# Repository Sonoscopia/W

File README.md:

# W
W: Staged concert for robotic orchestra and puppets
A co-creation of Sonoscopia and Teatro de Ferro
Homepage is [here](https://sonoscopia.pt/en/works/w-en/)

## Contents of this repository: 
- SRC01: 8 channel relay controller with MIDI IN/THRU and 8 arcade buttons
- Servo8: 8 channel servo controller with MIDI IN/THRU and 8 knobs
- Stepper5: 5 channel stepper motor controller with MIDI IN/THRU and 5 encoders (if I remember correctly...)

## Description
W is a staged concert for puppets, robotic orchestra and video that departs from the theme of work, human liberation and the logic of power, subjugation and domination initiated with the development of Phobos – Dysfunctional Robotic Orchestra. These issues, exposed in a subliminal and essentially musical way in Phobos’ original conception, now move to a clear dramaturgical level and are reinforced by the text, gesture, body, video and scenic space that highlights all the developed sound elements.

W is the physical symbol of the work and this staged concert is itself the result of thousands of hours of work. But what is work anyway?
The play traverses a diversity of places and imaginaries where this strange form of life thrives, simultaneously liberating and oppressive, which has transformed the world into a large shipyard, a large shopping centre.

Somewhere between the expulsion from the earthly paradise, from which we began to eat bread made with the sweat of our brows, and the hegemony of the neoliberal paradigm – in which sweat, bread or face are mere assets that each individual entrepreneur may or may not access – there is a place to look. W!

## Credits
- Project conception and management: Gustavo Costa
- Staging, Scenography and Dramaturgy – Igor Gandra
- Plastic Realization and Construction – Eduardo Mendes
- Light design: Mariana Figueroa
- Composition and musical direction: Gustavo Costa
- Interpretation: Adriana Romero, Alberto Lopes, Carla Veloso, Eduardo Mendes, Gustavo Costa, Henrique Fernandes, Igor Gandra, Jorge Quintela and Tiago Ângelo
- Support for electronics and programming: Tiago Ângelo
- Instrument building: Alberto Lopes, Henrique Fernandes and Gustavo Costa
- Video: Jorge Quintela
- Construction of the scenography, puppets and props: Eduardo Mendes, Hernâni Miranda, Gonçalo Silva (trainee at the Professional School of the Campanhã Youth Center), Solveig Phyllis Rocher, Américo Castanheira
- Executive Production: Carla Veloso and Patrícia Caveiro
- Production support: Catarina Lopes
- Production: Sonoscopy and Teatro de Ferro
- Co-production: Teatro Municipal do Porto
- Partnership: 23 Miles
- Project supported by the Portuguese Republic – Culture/Direção-Geral das Artes.
- Acknowledgements: Hugo de Almeida Pinho, Regina Guimarães

## LICENSE
[![CC BY-NC 4.0][cc-by-nc-shield]][cc-by-nc]

This work is licensed under a
[Creative Commons Attribution-NonCommercial 4.0 International License][cc-by-nc].

[![CC BY-NC 4.0][cc-by-nc-image]][cc-by-nc]

[cc-by-nc]: https://creativecommons.org/licenses/by-nc/4.0/
[cc-by-nc-image]: https://licensebuttons.net/l/by-nc/4.0/88x31.png
[cc-by-nc-shield]: https://img.shields.io/badge/License-CC%20BY--NC%204.0-lightgrey.svg

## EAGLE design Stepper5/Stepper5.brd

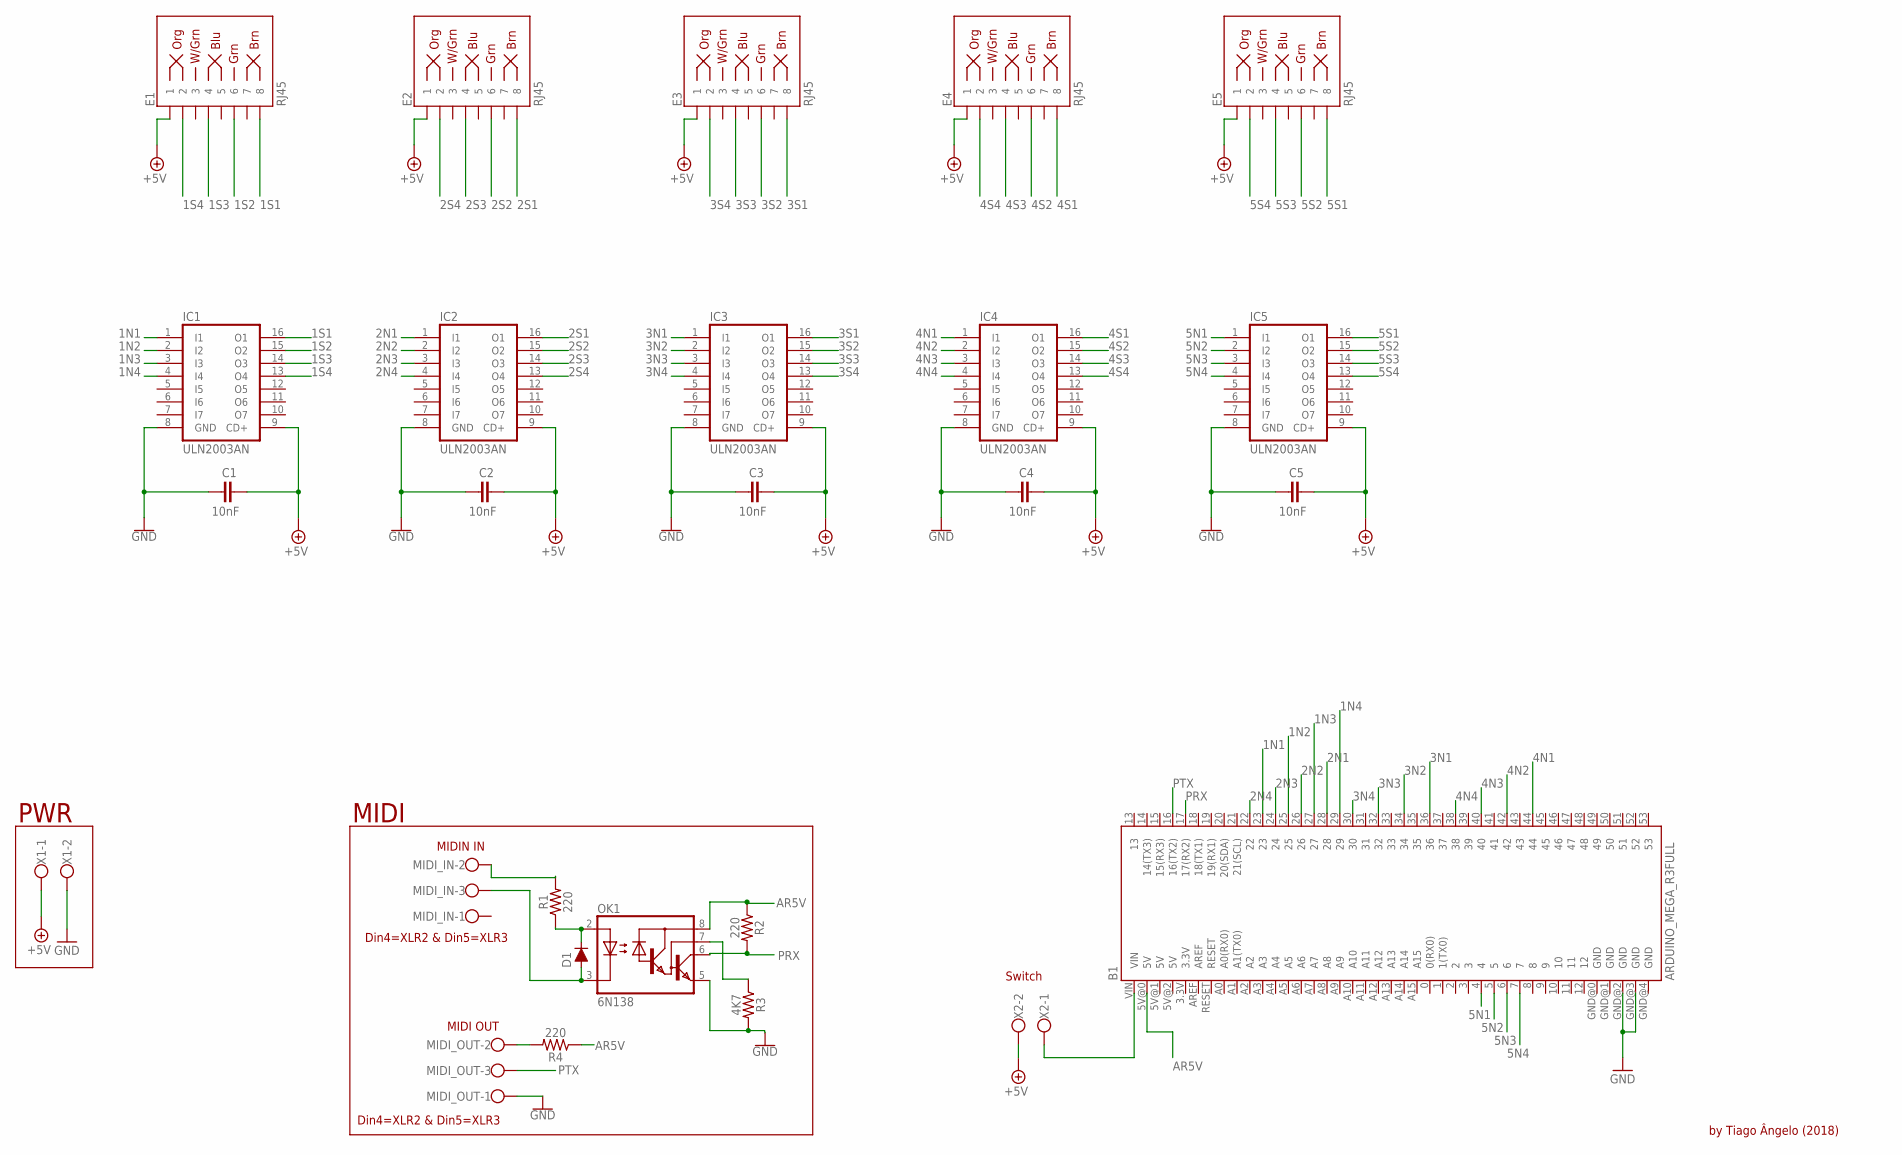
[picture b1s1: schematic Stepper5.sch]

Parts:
B1: ARDUINO_MEGA_R3FULL; ARDUINO_MEGA
C1, C2, C3, C4, C5: 10nF; C5B2.5
D1: 200mA/100V/1V; DIODE-1N4148
E1, E2, E3, E4, E5: RJ45; RJ45-8
IC1, IC2, IC3, IC4, IC5: ULN2003AN; DIL16
MIDI_IN: W237-103
MIDI_OUT: W237-103
OK1: 6N138; DIL08
R1, R2, R4: 220; AXIAL-0.3
R3: 4K7; AXIAL-0.3
X1, X2: W237-102

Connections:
1N1: B1.23, IC1.1 (I1)
1N2: B1.25, IC1.2 (I2)
1N3: B1.27, IC1.3 (I3)
1N4: B1.29, IC1.4 (I4)
1S1: E1.8, IC1.16 (O1)
1S2: E1.6, IC1.15 (O2)
1S3: E1.4, IC1.14 (O3)
1S4: E1.2, IC1.13 (O4)
2N1: B1.28, IC2.1 (I1)
2N2: B1.26, IC2.2 (I2)
2N3: B1.24, IC2.3 (I3)
2N4: B1.22, IC2.4 (I4)
2S1: E2.8, IC2.16 (O1)
2S2: E2.6, IC2.15 (O2)
2S3: E2.4, IC2.14 (O3)
2S4: E2.2, IC2.13 (O4)
3N1: B1.36, IC3.1 (I1)
3N2: B1.34, IC3.2 (I2)
3N3: B1.32, IC3.3 (I3)
3N4: B1.30, IC3.4 (I4)
3S1: E3.8, IC3.16 (O1)
3S2: E3.6, IC3.15 (O2)
3S3: E3.4, IC3.14 (O3)
3S4: E3.2, IC3.13 (O4)
4N1: B1.44, IC4.1 (I1)
4N2: B1.42, IC4.2 (I2)
4N3: B1.40, IC4.3 (I3)
4N4: B1.38, IC4.4 (I4)
4S1: E4.8, IC4.16 (O1)
4S2: E4.6, IC4.15 (O2)
4S3: E4.4, IC4.14 (O3)
4S4: E4.2, IC4.13 (O4)
5N1: B1.4, IC5.1 (I1)
5N2: B1.5, IC5.2 (I2)
5N3: B1.6, IC5.3 (I3)
5N4: B1.7, IC5.4 (I4)
5S1: E5.8, IC5.16 (O1)
5S2: E5.6, IC5.15 (O2)
5S3: E5.4, IC5.14 (O3)
5S4: E5.2, IC5.13 (O4)
+5V: C1.2, C2.2, C3.2, C4.2, C5.2, E1.1, E2.1, E3.1, E4.1, E5.1, IC1.9 (CD+), IC2.9 (CD+), IC3.9 (CD+), IC4.9 (CD+), IC5.9 (CD+), X1.1, X2.2
AR5V: B1.5V@0 (5V), OK1.8 (VCC), R2.P$1 (1), R4.P$1 (1)
GND: B1.GND@2 (GND), B1.GND@3 (GND), C1.1, C2.1, C3.1, C4.1, C5.1, IC1.8 (GND), IC2.8 (GND), IC3.8 (GND), IC4.8 (GND), IC5.8 (GND), MIDI_OUT.1, OK1.5 (GND), R3.P$2 (2), X1.2
unnamed: B1.VIN, X2.1
unnamed: MIDI_OUT.2, R4.P$2 (2)
unnamed: D1.A, MIDI_IN.3, OK1.3 (C)
unnamed: D1.C, OK1.2 (A), R1.P$1 (1)
unnamed: MIDI_IN.2, R1.P$2 (2)
unnamed: OK1.7 (VB), R3.P$1 (1)
PRX: B1.17 (17(RX2)), OK1.6 (VO), R2.P$2 (2)
PTX: B1.16 (16(TX2)), MIDI_OUT.3

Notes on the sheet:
Din4=XLR2 & Din5=XLR3
MIDI OUT
MIDIN IN
MIDI
PWR
by Tiago Ângelo (2018)
Switch

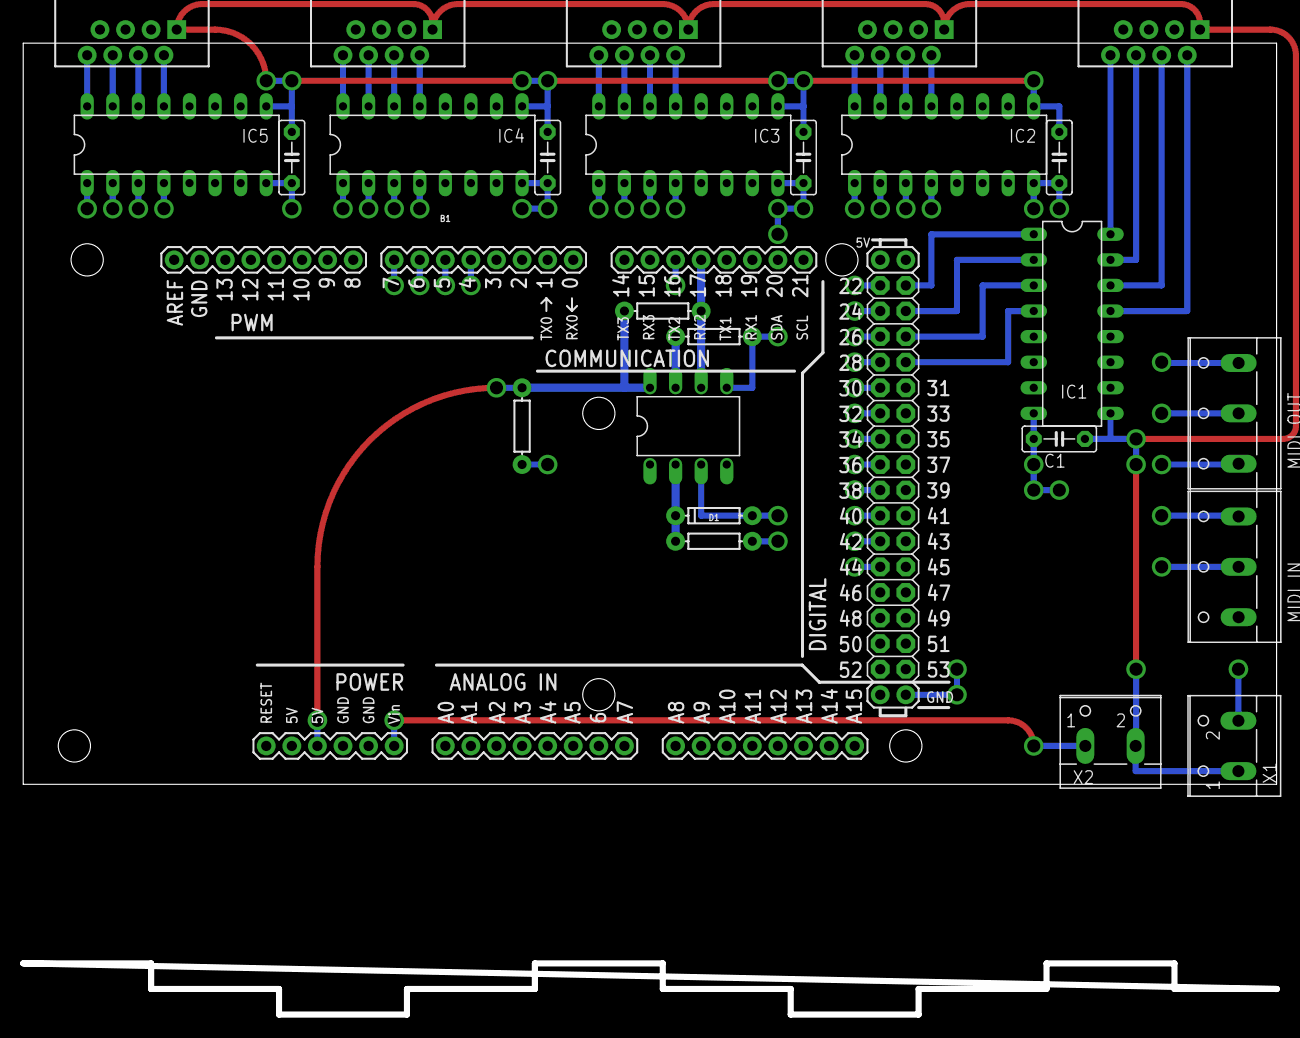
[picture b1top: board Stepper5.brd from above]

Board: 5 copper layers, 124.4 x 73.6 mm, 26 parts (0 on the bottom side), 51 nets.

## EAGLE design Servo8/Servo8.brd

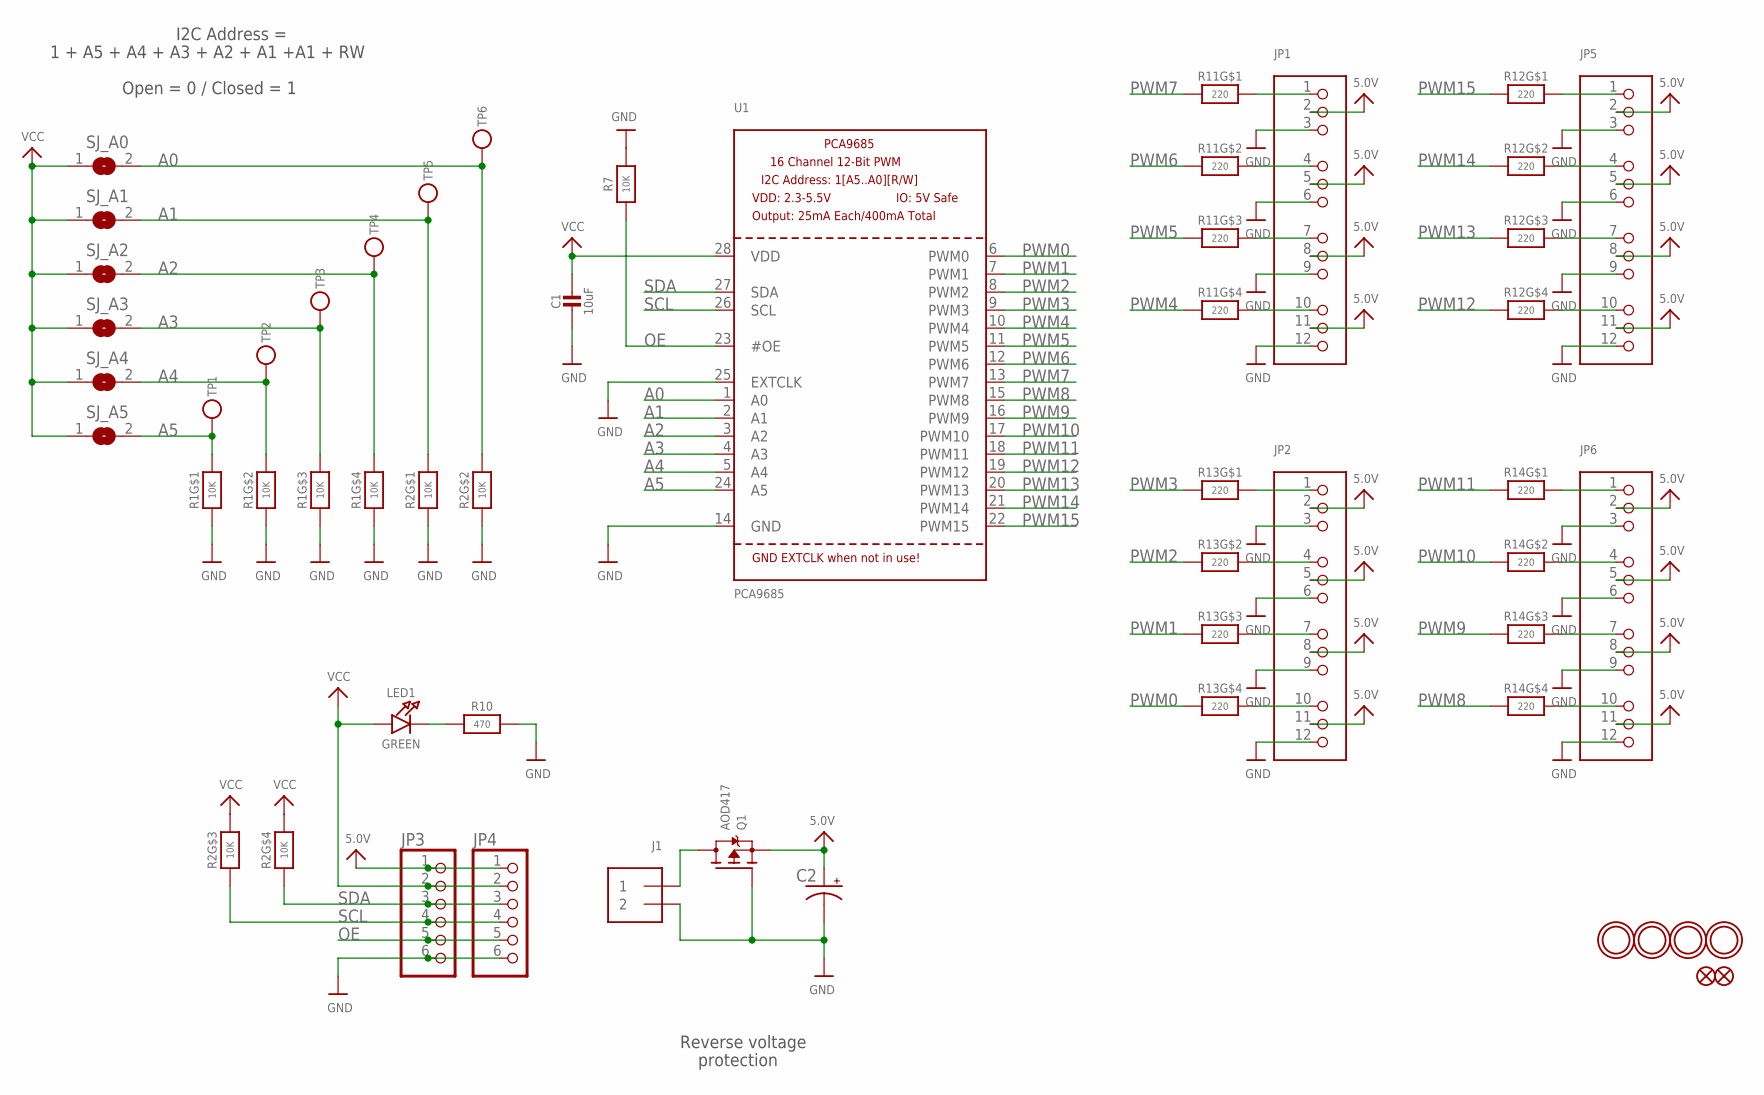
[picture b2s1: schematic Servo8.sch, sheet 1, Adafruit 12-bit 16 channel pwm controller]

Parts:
C1: 10uF; 0805-NO
C2: CPOL-USE3.5-8; E3,5-8
FID1, FID2: FIDUCIAL""; FIDUCIAL_1MM
J1: TERMBLOCK_1X2; TERMBLOCK_1X2-3.5MM
JP1, JP2, JP5, JP6: HEADER-3X04; 3X04
JP3, JP4: PINHD-1X6CB; 1X06-CLEANBIG
LED1: GREEN; CHIPLED_0805_NOOUTLINE
Q1: AOD417; TO252
R1, R2: 10K; RESPACK_4X0603
R7: 10K; 0805-NO
R10: 470; _0805MP
R11, R12, R13, R14: 220; RESPACK_4X0603
SJ_A0, SJ_A1, SJ_A2, SJ_A3, SJ_A4, SJ_A5: SOLDERJUMPERREFLOW_NOPASTE; SOLDERJUMPER_REFLOW_NOPASTE
TP1, TP2, TP3, TP4, TP5, TP6: TESTPOINTROUND1MM; TESTPOINT_ROUND_1MM
U1: PCA9685; TSSOP28
U$47, U$48, U$49, U$50: MOUNTINGHOLE2.5; MOUNTINGHOLE_2.5_PLATED

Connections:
5.0V: C2.+, JP1.2, JP1.5, JP1.8, JP1.11, JP2.2, JP2.5, JP2.8, JP2.11, JP3.1, JP4.1, JP5.2, JP5.5, JP5.8, JP5.11, JP6.2, JP6.5, JP6.8, JP6.11, Q1.2 (S); also elsewhere on the board
A0: R2.7 (2), SJ_A0.2, TP6.P$1, U1.1 (A0)
A1: R2.8 (2), SJ_A1.2, TP5.P$1, U1.2 (A1)
A2: R1.5 (2), SJ_A2.2, TP4.P$1, U1.3 (A2)
A3: R1.6 (2), SJ_A3.2, TP3.P$1, U1.4 (A3)
A4: R1.7 (2), SJ_A4.2, TP2.P$1, U1.5 (A4)
A5: R1.8 (2), SJ_A5.2, TP1.P$1, U1.24 (A5)
GND: C1.2, C2.-, J1.2, JP1.3, JP1.6, JP1.9, JP1.12, JP2.3, JP2.6, JP2.9, JP2.12, JP3.6, JP4.6, JP5.3, JP5.6, JP5.9, JP5.12, JP6.3, JP6.6, JP6.9, JP6.12, Q1.1 (G), R1.1, R1.2 (1), R1.3 (1), R1.4 (1), R2.1, R2.2 (1), R7.2, R10.2, U1.14 (GND), U1.25 (EXTCLK); also elsewhere on the board
unnamed: LED1.C, R10.1
unnamed: JP1.4, R11.7 (2)
unnamed: JP1.1, R11.8 (2)
unnamed: JP1.7, R11.6 (2)
unnamed: JP1.10, R11.5 (2)
unnamed: JP2.1, R13.8 (2)
unnamed: JP2.4, R13.7 (2)
unnamed: JP2.7, R13.6 (2)
unnamed: JP2.10, R13.5 (2)
unnamed: JP6.10, R14.5 (2)
unnamed: JP6.7, R14.6 (2)
unnamed: JP6.4, R14.7 (2)
unnamed: JP6.1, R14.8 (2)
unnamed: JP5.10, R12.5 (2)
unnamed: JP5.7, R12.6 (2)
unnamed: JP5.4, R12.7 (2)
unnamed: JP5.1, R12.8 (2)
OE: JP3.5, JP4.5, R7.1, U1.23 (#OE)
PWM0: R13.4 (1), U1.6 (PWM0)
PWM1: R13.3 (1), U1.7 (PWM1); also elsewhere on the board
PWM2: R13.2 (1), U1.8 (PWM2); also elsewhere on the board
PWM3: R13.1, U1.9 (PWM3); also elsewhere on the board
PWM4: R11.4 (1), U1.10 (PWM4); also elsewhere on the board
PWM5: R11.3 (1), U1.11 (PWM5); also elsewhere on the board
PWM6: R11.2 (1), U1.12 (PWM6); also elsewhere on the board
PWM7: R11.1, U1.13 (PWM7); also elsewhere on the board
PWM8: R14.4 (1), U1.15 (PWM8); also elsewhere on the board
PWM9: R14.3 (1), U1.16 (PWM9)
PWM10: R14.2 (1), U1.17 (PWM10)
PWM11: R14.1, U1.18 (PWM11)
PWM12: R12.4 (1), U1.19 (PWM12)
PWM13: R12.3 (1), U1.20 (PWM13)
PWM14: R12.2 (1), U1.21 (PWM14)
PWM15: R12.1, U1.22 (PWM15)
PWRIN: J1.1, Q1.3 (D)
SCL: JP3.4, JP4.4, R2.3 (1), U1.26 (SCL); also elsewhere on the board
SDA: JP3.3, JP4.3, R2.4 (1), U1.27 (SDA); also elsewhere on the board
VCC: C1.1, JP3.2, JP4.2, LED1.A, R2.5 (2), R2.6 (2), SJ_A0.1, SJ_A1.1, SJ_A2.1, SJ_A3.1, SJ_A4.1, SJ_A5.1, U1.28 (VDD); also elsewhere on the board

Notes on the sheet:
Reverse voltage
protection
1 + A5 + A4 + A3 + A2 + A1 +A1 + RW
I2C Address =
Open = 0 / Closed = 1

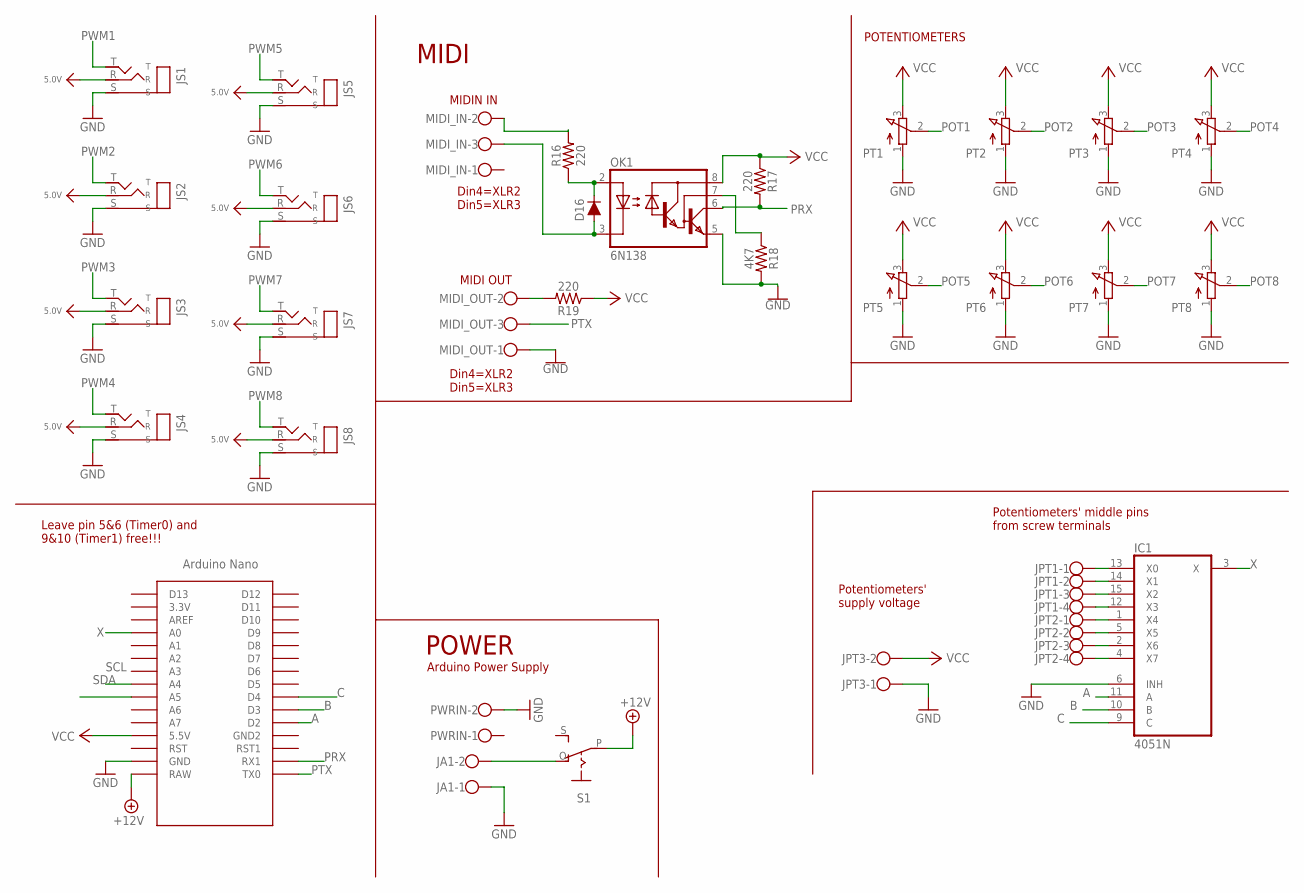
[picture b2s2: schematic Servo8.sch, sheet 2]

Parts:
D16: 200mA/100V/1V; DIODE-1N4148
IC1: 4051N; DIL16
JA1: W237-102
JPT1, JPT2: W237-4
JPT3: W237-102
JS1, JS2, JS3, JS4, JS5, JS6, JS7, JS8: STEREOREV; STEREO_JACK_MIRROR
MIDI_IN: W237-103
MIDI_OUT: W237-103
OK1: 6N138; DIL08
PT1, PT2, PT3, PT4, PT5, PT6, PT7, PT8: 3RP/1610N
PWRIN: W237-4
R16, R17, R19: 220; AXIAL-0.3
R18: 4K7; AXIAL-0.3
S1: EG1218S; EG1218
U$55: NANO

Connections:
5.0V: JS1.R, JS2.R, JS3.R, JS4.R, JS5.R, JS6.R, JS7.R, JS8.R; also elsewhere on the board
+12V: S1.P, U$55.RAW
A: IC1.11 (A), U$55.D2
B: IC1.10 (B), U$55.D3
C: IC1.9 (C), U$55.D4
GND: IC1.6 (INH), IC1.8 (GND), JA1.1, JPT3.1, JS1.S, JS2.S, JS3.S, JS4.S, JS5.S, JS6.S, JS7.S, JS8.S, MIDI_OUT.1, OK1.5 (GND), PT1.1 (A), PT2.1 (A), PT3.1 (A), PT4.1 (A), PT5.1 (A), PT6.1 (A), PT7.1 (A), PT8.1 (A), PWRIN.2, R18.P$2 (2), U$55.GND; also elsewhere on the board
unnamed: JA1.2, S1.O
unnamed: MIDI_OUT.2, R19.P$2 (2)
unnamed: D16.A, MIDI_IN.3, OK1.3 (C)
unnamed: D16.C, OK1.2 (A), R16.P$1 (1)
unnamed: MIDI_IN.2, R16.P$2 (2)
unnamed: OK1.7 (VB), R18.P$1 (1)
POT1: IC1.13 (X0), JPT1.1, PT1.2 (S)
POT2: IC1.14 (X1), JPT1.2, PT2.2 (S)
POT3: IC1.15 (X2), JPT1.3, PT3.2 (S)
POT4: IC1.12 (X3), JPT1.4, PT4.2 (S)
POT5: IC1.1 (X4), JPT2.1, PT5.2 (S)
POT6: IC1.5 (X5), JPT2.2, PT6.2 (S)
POT7: IC1.2 (X6), JPT2.3, PT7.2 (S)
POT8: IC1.4 (X7), JPT2.4, PT8.2 (S)
PRX: OK1.6 (VO), R17.P$2 (2), U$55.RX1
PTX: MIDI_OUT.3, U$55.TX0
PWM1: JS1.T; also elsewhere on the board
PWM2: JS2.T; also elsewhere on the board
PWM3: JS3.T; also elsewhere on the board
PWM4: JS4.T; also elsewhere on the board
PWM5: JS5.T; also elsewhere on the board
PWM6: JS6.T; also elsewhere on the board
PWM7: JS7.T; also elsewhere on the board
PWM8: JS8.T; also elsewhere on the board
SCL: U$55.A5; also elsewhere on the board
SDA: U$55.A4; also elsewhere on the board
VCC: IC1.16 (VCC), JPT3.2, OK1.8 (VCC), PT1.3 (E), PT2.3 (E), PT3.3 (E), PT4.3 (E), PT5.3 (E), PT6.3 (E), PT7.3 (E), PT8.3 (E), R17.P$1 (1), R19.P$1 (1), U$55.5V (5.5V); also elsewhere on the board
VEE: IC1.7 (VEE)
X: IC1.3 (X), U$55.A0

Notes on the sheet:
Leave pin 5&6 (Timer0) and 9&10 (Timer1) free!!!
Arduino Power Supply
Potentiometers' supply voltage
POTENTIOMETERS
Potentiometers' middle pins from screw terminals
POWER
Din4=XLR2 Din5=XLR3
MIDI OUT
MIDIN IN
MIDI

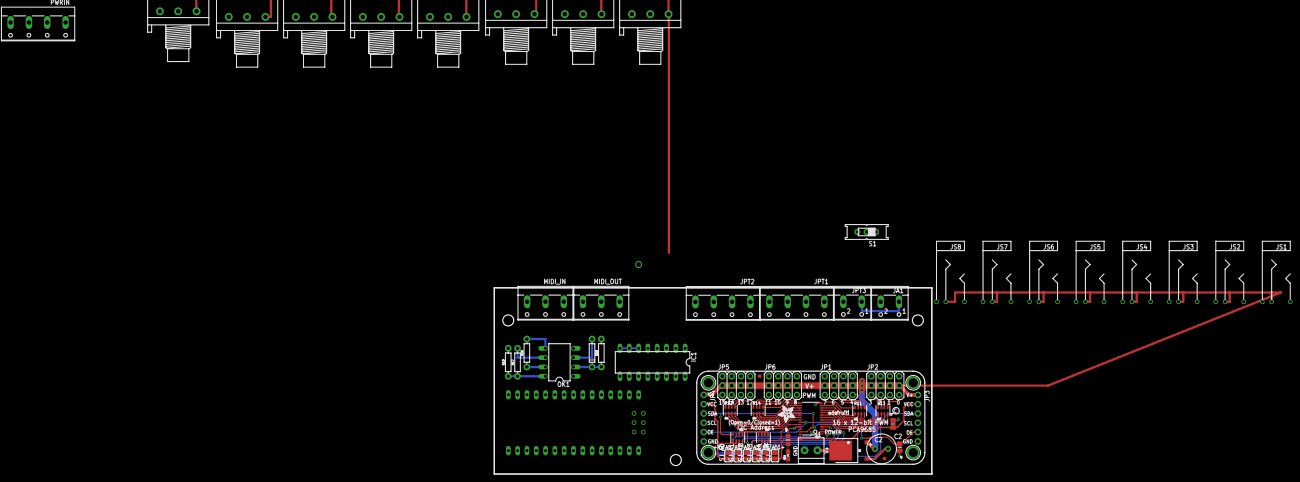
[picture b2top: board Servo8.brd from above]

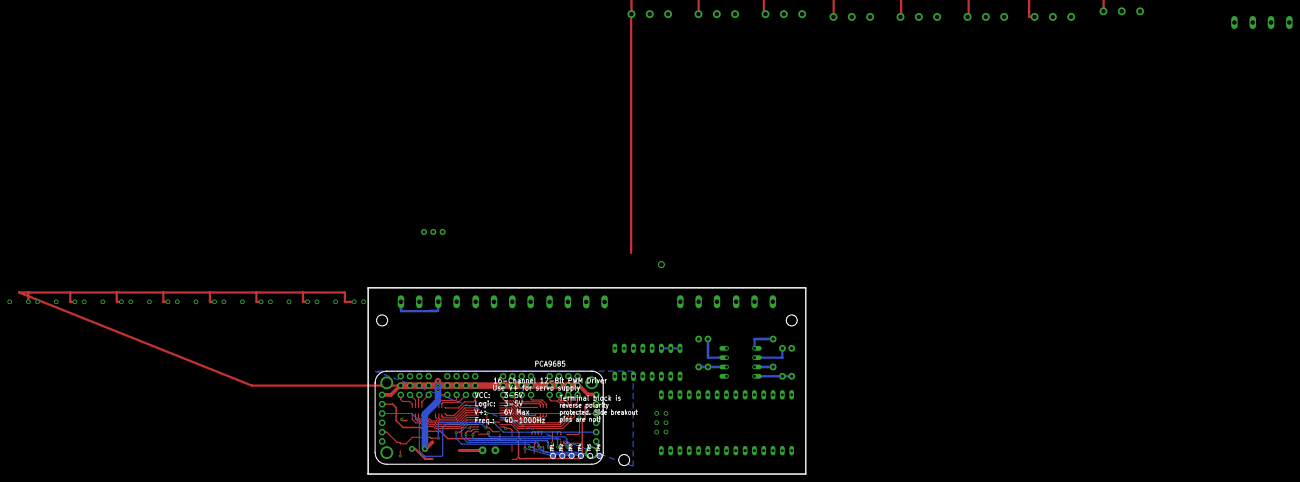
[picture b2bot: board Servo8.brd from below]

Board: 4 copper layers, 119.4 x 50.8 mm, 72 parts (6 on the bottom side), 67 nets.

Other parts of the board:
U$51: ADAFRUIT_5MM
U$54: PCBFEAT-REV-040

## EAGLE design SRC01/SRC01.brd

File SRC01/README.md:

# PHOBOS - RELAY CONTROLLER

## MIDI INPUT

- midi channel 1
- notes 96 to 103

## POWER 

- arcade box: 9VDC >360mA center tap positive (or 7~12V : it has an additional 7812 voltage reg) 
- relay box: 5VDC > 160mA center tap positive (15-20mA per channel) input, 250VAC 10A or 30VDC 10A per output channel

## CONNECTIONS

- VGA cable between arcade and relay boxes
- MIDI input via XLR (see PHOBOS repository) 
- MIDI out/thru via XLR 
- power in/out(thru) via micro sockets (see PHOBOS repository) 

### VGA CONNECTIONS

- 4, 5, 6, 7, 8, 11: GND
- 1: R1
- 2: R2
- 3: R3
- 9: R4
- 10: R5
- 12: R6
- 13: R7
- 14: R8
- 15: +5V

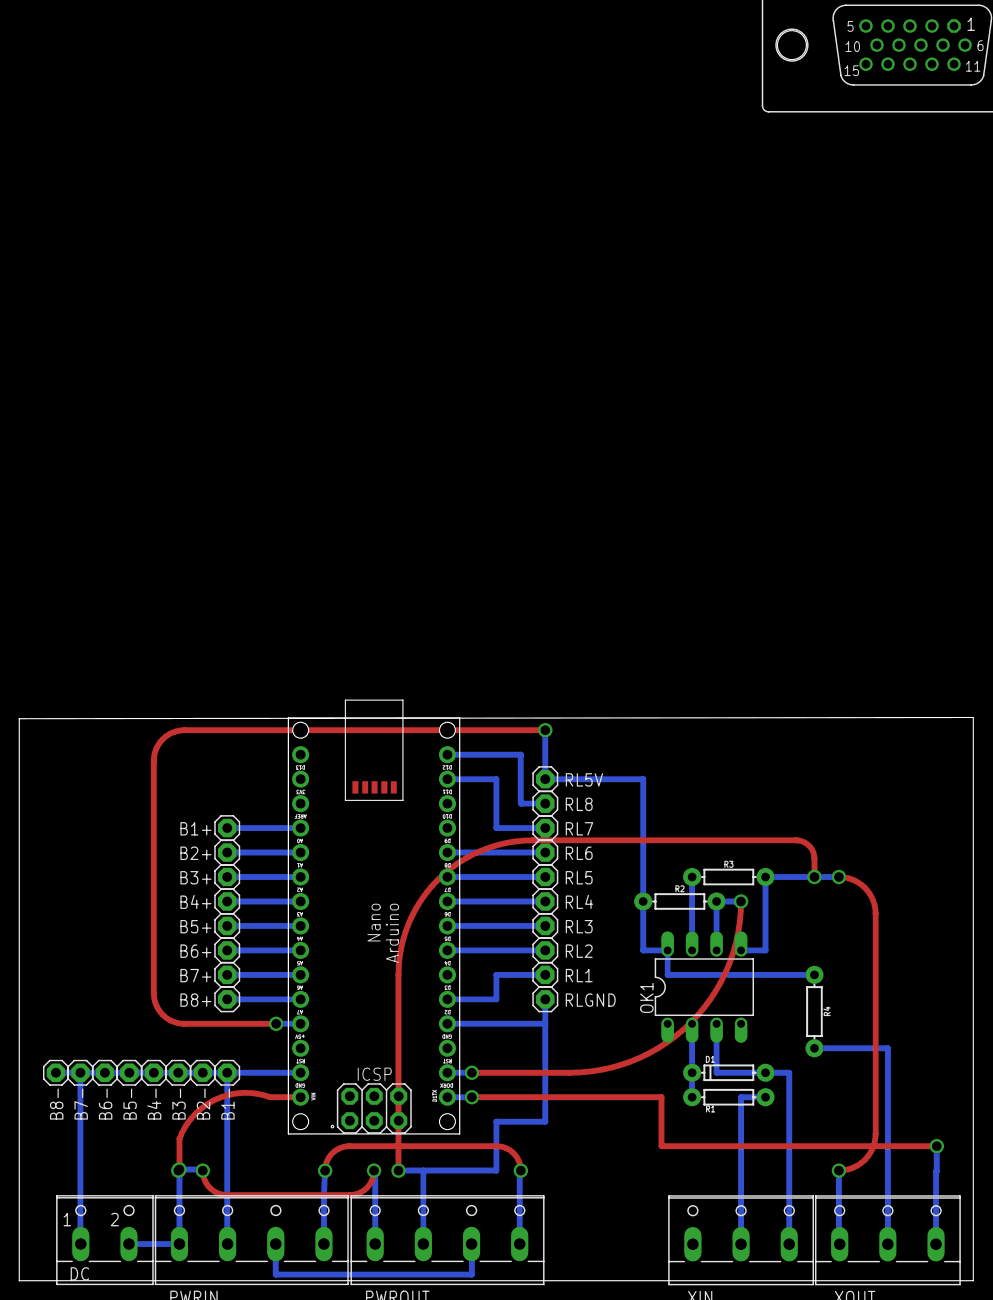
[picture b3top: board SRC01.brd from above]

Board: 2 copper layers, 99.0 x 58.5 mm, 39 parts (0 on the bottom side), 28 nets.

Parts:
B1+, B1-, B2+, B2-, B3+, B3-, B4+, B4-, B5+, B5-, B6+, B6-, B7+, B7-, B8+, B8-: 1X01
D1: 200mA/100V/1V; DIODE-1N4148
DC: W237-102
OK1: 6N138; DIL08
PCB1: ARDUINO_NANO
PWRIN: W237-4
PWROUT: W237-4
R1, R2, R4: 220; AXIAL-0.3
R3: 4K7; AXIAL-0.3
RL1, RL2, RL3, RL4, RL5, RL5V, RL6, RL7, RL8: 1X01
RLGND: 1X01
X1: HDF15V
XIN: W237-103
XOUT: W237-103

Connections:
5VM: PWRIN.4, PWROUT.4
12VA: DC.2, PCB1.VIN, PWRIN.1, PWROUT.1
12VL: PWRIN.3, PWROUT.3
AR5V: OK1.8, PCB1.5V, R2.P$1, R4.P$1, RL5V.1, X1.14
B1: B1+.1, PCB1.A0
B2: B2+.1, PCB1.A1
B3: B3+.1, PCB1.A2
B4: B4+.1, PCB1.A3
B5: B5+.1, PCB1.A4
B6: B6+.1, PCB1.A5
B7: B7+.1, PCB1.A6
B8: B8+.1, PCB1.A7
D1: PCB1.D2, RL1.1, X1.1
D2: PCB1.D4, RL2.1, X1.2
D3: PCB1.D5, RL3.1, X1.3
D4: PCB1.D6, RL4.1, X1.4
D5: PCB1.D7, RL5.1, X1.5
D6: PCB1.D8, RL6.1, X1.6
D7: PCB1.D11, RL7.1, X1.7
D8: PCB1.D12, RL8.1, X1.8
GND: B1-.1, B2-.1, B3-.1, B4-.1, B5-.1, B6-.1, B7-.1, B8-.1, DC.1, OK1.5, PCB1.GND, PCB1.GND., PWRIN.2, PWROUT.2, R3.P$2, RLGND.1, X1.15, XOUT.1
unnamed: R4.P$2, XOUT.2
unnamed: D1.A, OK1.3, XIN.3
unnamed: D1.C, OK1.2, R1.P$1
unnamed: R1.P$2, XIN.2
unnamed: OK1.7, R3.P$1
PRX: OK1.6, PCB1.RX1, R2.P$2
PTX: PCB1.TX1, XOUT.3

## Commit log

2025-08-14 updated from local
2025-08-14 added license and updated README

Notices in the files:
parts and their libraries:
SparkFun-DiscreteSemi: Licensing: Creative Commons ShareAlike 4.0 International - https://creativecommons.org/licenses/by-sa/4.0
